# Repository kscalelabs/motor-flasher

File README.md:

# can-daddy-atopile

Wooohooo a new package!

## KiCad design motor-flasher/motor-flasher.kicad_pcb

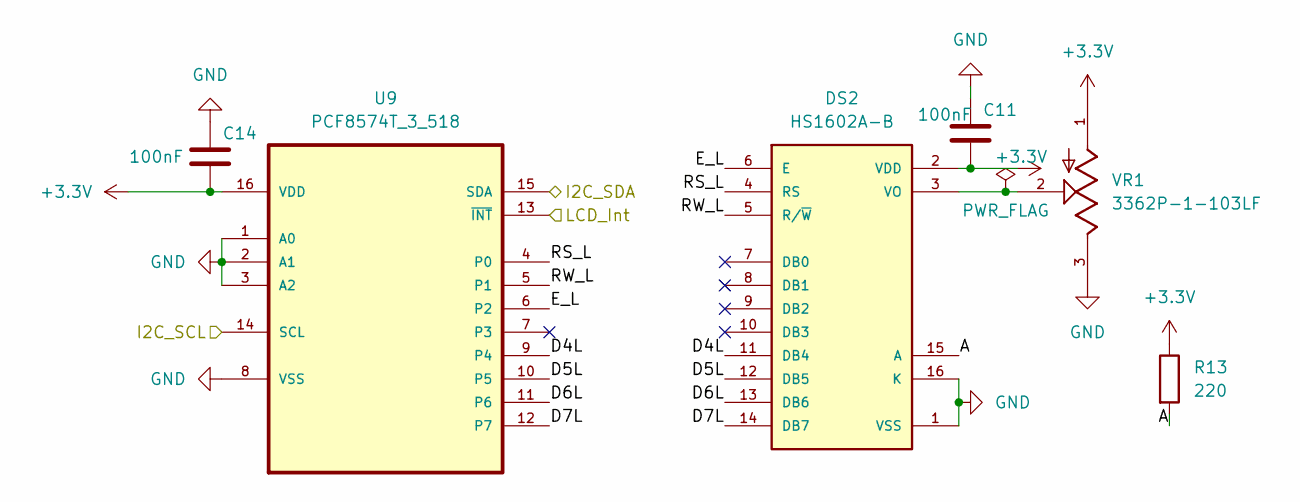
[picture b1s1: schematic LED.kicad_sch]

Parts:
C11, C14: 100nF; C_0402_1005Metric
DS2: HS1602A-B; LCD_LCM-S01602DTR_A
R13: 220; R_0402_1005Metric
U9: PCF8574T_3_518; SOIC127P1032X265-16N; MPN PCF8574T/3,518
VR1: 3362P-1-103LF; POT_3362P; PARTREV 08/26/10

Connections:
+3.3V: C11.2, C14.2, DS2.2 (VDD), R13.1, U9.16 (VDD), VR1.1; also elsewhere on the board
/LCD/A: DS2.15 (A), R13.2
/LCD/D4L: DS2.11 (DB4), U9.9 (P4)
/LCD/D5L: DS2.12 (DB5), U9.10 (P5)
/LCD/D6L: DS2.13 (DB6), U9.11 (P6)
/LCD/D7L: DS2.14 (DB7), U9.12 (P7)
/LCD/E_L: DS2.6 (E), U9.6 (P2)
/LCD/RS_L: DS2.4 (RS), U9.4 (P0)
/LCD/RW_L: DS2.5 (R/~W), U9.5 (P1)
/LCD_Int: U9.13 (~INT); also elsewhere on the board
/SCL: U9.14 (SCL); also elsewhere on the board
/SDA: U9.15 (SDA); also elsewhere on the board
GND: C11.1, C14.1, DS2.1 (VSS), DS2.16 (K), U9.1 (A0), U9.2 (A1), U9.3 (A2), U9.8 (VSS), VR1.3; also elsewhere on the board
unnamed: DS2.3 (VO), VR1.2

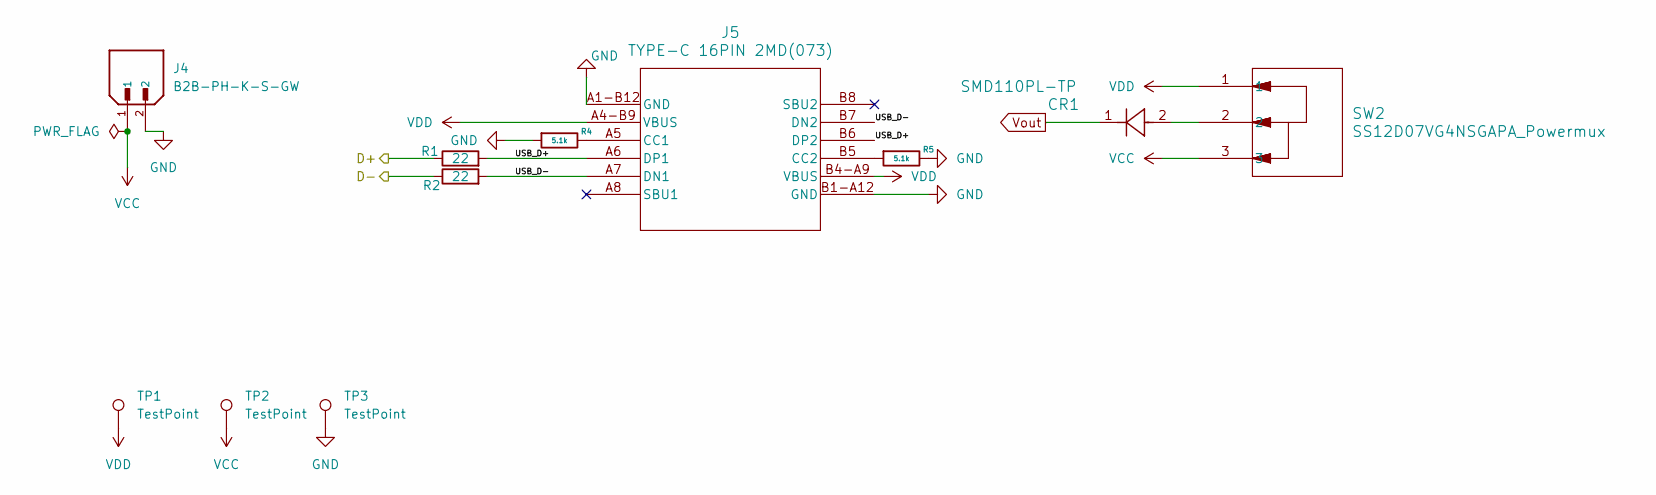
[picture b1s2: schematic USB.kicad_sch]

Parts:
CR1: SMD110PL-TP; SOD-123FL_MCC
J4: B2B-PH-K-S-GW; JST_B2B-XH-A; PARTREV N/A
J5: TYPE-C 16PIN 2MD(073); GCT_USB4105-GF-A
R1, R2: 22; R_0402_1005Metric
R4, R5: 5.1k; R_0603_1608Metric
SW2: SS12D07VG4NSGAPA_Powermux; SS12D07_CNK
TP1, TP2, TP3: TestPoint

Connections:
/D+: R1.1; also elsewhere on the board
/D-: R2.1; also elsewhere on the board
/USB + Power Source/USB_D+: J5.A6 (DP1), J5.B6 (DP2), R1.2
/USB + Power Source/USB_D-: J5.A7 (DN1), J5.B7 (DN2), R2.2
GND: J4.2, J5.A1-B12 (GND), J5.B1-A12 (GND), R4.2, R5.1, TP3.1; also elsewhere on the board
unnamed: CR1.2, SW2.2
unnamed: J5.A5 (CC1), R4.1
unnamed: J5.B5 (CC2), R5.2
VCC: J4.1, SW2.3, TP2.1
VDD: J5.A4-B9 (VBUS), J5.B4-A9 (VBUS), SW2.1, TP1.1
Vout: CR1.1; also elsewhere on the board

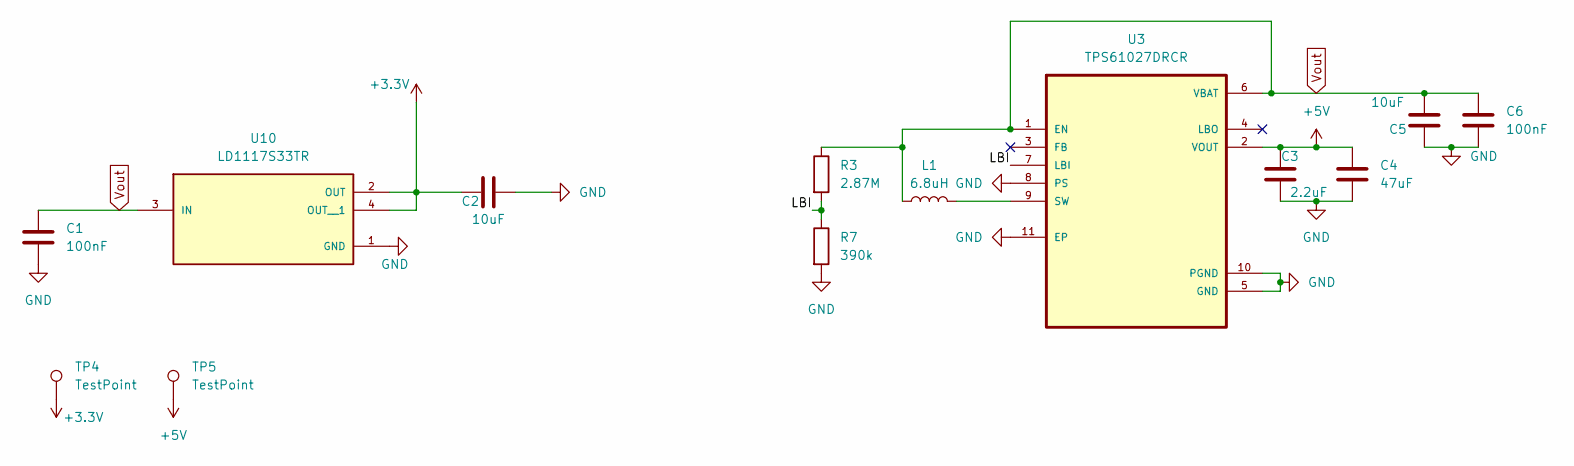
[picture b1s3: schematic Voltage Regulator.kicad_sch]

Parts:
C1, C6: 100nF; C_0402_1005Metric
C2, C5: 10uF; C_0805_2012Metric
C3: 2.2uF; C_0402_1005Metric
C4: 47uF; C_0805_2012Metric
L1: 6.8uH; CDRH5D28RHP
R3: 2.87M; R_0805_2012Metric
R7: 390k; R_0805_2012Metric
TP4, TP5: TestPoint
U3: TPS61027DRCR; VREG_V62_16624-01YE
U10: LD1117S33TR; SOT230P700X180-4N

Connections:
+3.3V: C2.2, TP4.1, U10.2 (OUT), U10.4 (OUT__1); also elsewhere on the board
+5V: C3.1, C4.1, TP5.1, U3.2 (VOUT); also elsewhere on the board
/Voltage Regulator/LBI: R3.2, R7.1, U3.7 (LBI)
GND: C1.2, C2.1, C3.2, C4.2, C5.1, C6.1, R7.2, U3.5 (GND), U3.8 (PS), U3.10 (PGND), U3.11 (EP), U10.1 (GND); also elsewhere on the board
unnamed: L1.2, U3.9 (SW)
Vout: C1.1, C5.2, C6.2, L1.1, R3.1, U3.1 (EN), U3.6 (VBAT), U10.3 (IN); also elsewhere on the board

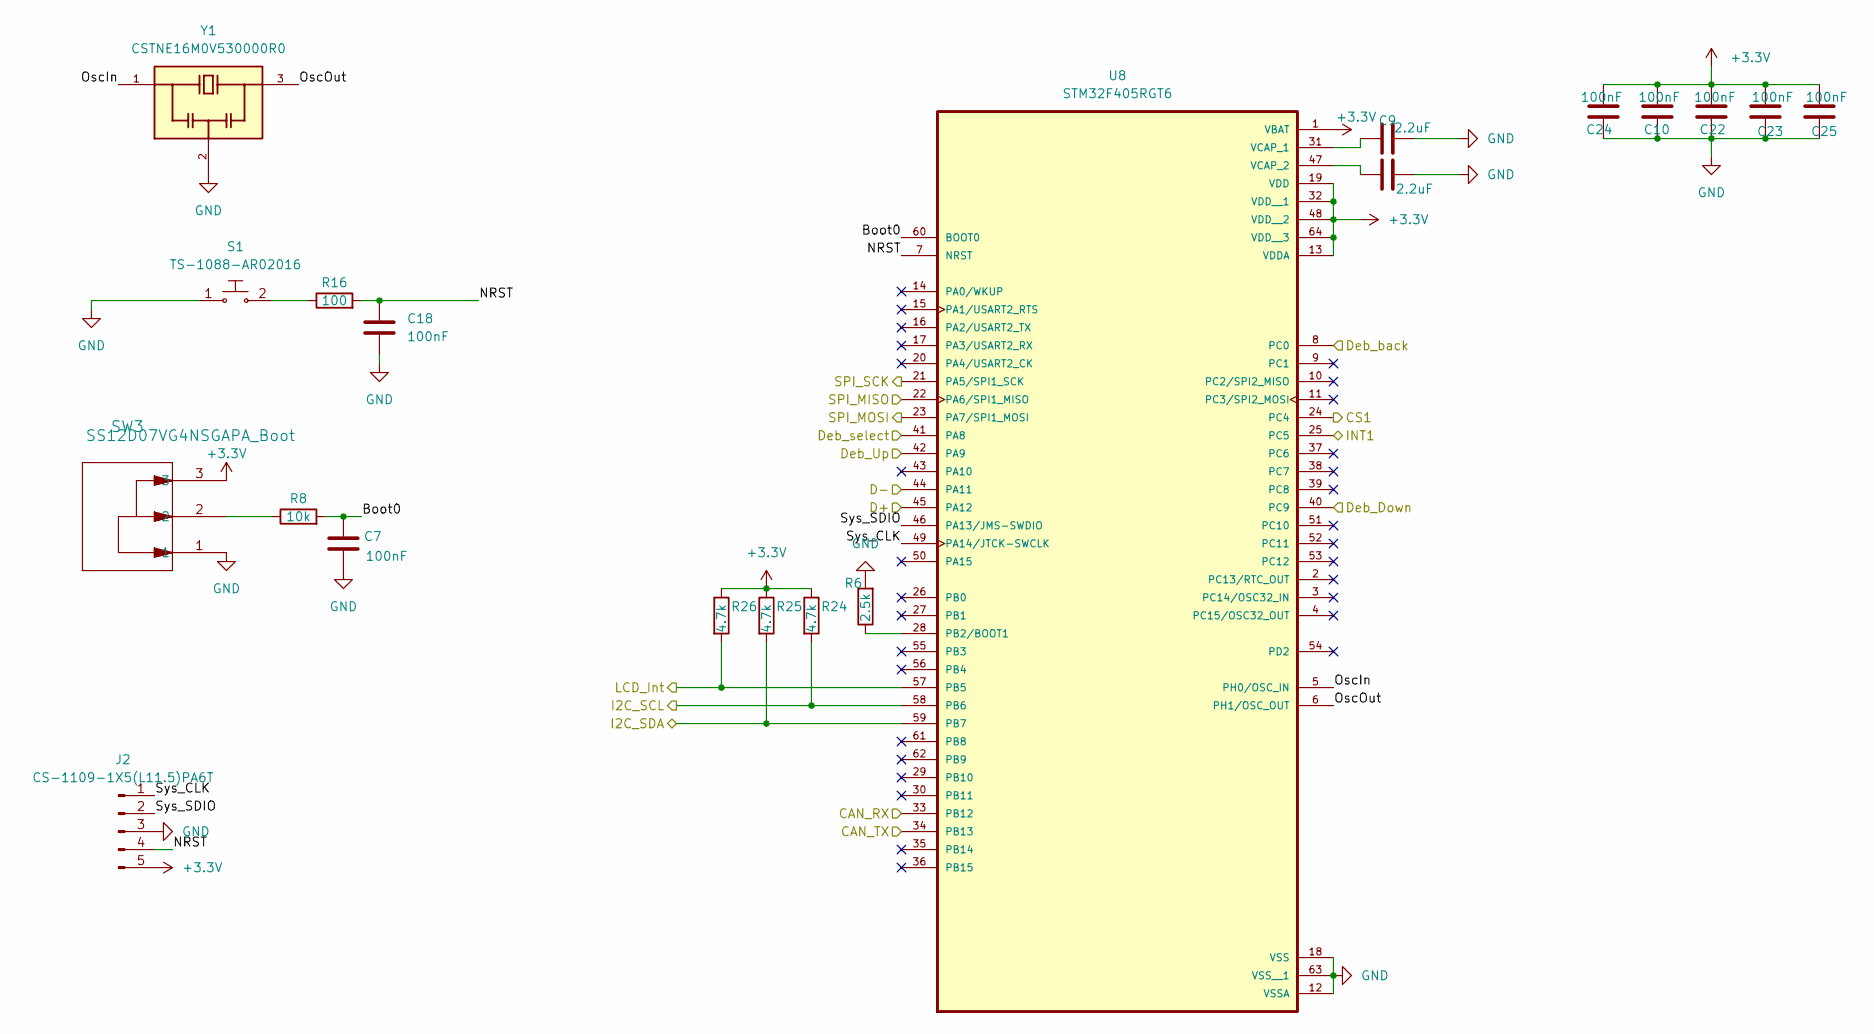
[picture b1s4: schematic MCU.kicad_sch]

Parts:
C7, C10, C18, C22, C23, C24, C25: 100nF; C_0402_1005Metric
C8, C9: 2.2uF; C_0402_1005Metric
J2: CS-1109-1X5(L11.5)PA6T; PinHeader_1x05_P2.54mm_Horizontal
R6: 2.5k; R_0603_1608Metric
R8: 10k; R_0402_1005Metric
R16: 100; R_0402_1005Metric
R24, R25, R26: 4.7k; R_0402_1005Metric
S1: TS-1088-AR02016; MPN GPTS203211B; Digi-Key_PN CW181-ND
SW3: SS12D07VG4NSGAPA_Boot; SS12D07_CNK
U8: STM32F405RGT6; QFP50P1200X1200X160-64N; PARTREV LTR
Y1: CSTNE16M0V530000R0; OSC_CSTNE16M0V530000R0; PARTREV JGC42-8853B

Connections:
+3.3V: C10.1, C22.1, C23.1, C24.1, C25.1, J2.5, R24.1, R25.1, R26.1, SW3.3, U8.1 (VBAT), U8.13 (VDDA), U8.19 (VDD), U8.32 (VDD__1), U8.48 (VDD__2), U8.64 (VDD__3); also elsewhere on the board
/CANRX: U8.33 (PB12); also elsewhere on the board
/CANTX: U8.34 (PB13); also elsewhere on the board
/CS: U8.24 (PC4); also elsewhere on the board
/D+: U8.45 (PA12); also elsewhere on the board
/D-: U8.44 (PA11); also elsewhere on the board
/Deb_Down: U8.40 (PC9); also elsewhere on the board
/Deb_Up: U8.42 (PA9); also elsewhere on the board
/Deb_back: U8.8 (PC0); also elsewhere on the board
/Deb_select: U8.41 (PA8); also elsewhere on the board
/INT: U8.25 (PC5); also elsewhere on the board
/LCD_Int: R26.2, U8.57 (PB5); also elsewhere on the board
/MCU/Boot0: C7.1, R8.2, U8.60 (BOOT0)
/MCU/NRST: C18.1, J2.4, R16.2, U8.7 (NRST)
/MCU/OscIn: U8.5 (PH0/OSC_IN), Y1.1
/MCU/OscOut: U8.6 (PH1/OSC_OUT), Y1.3
/MCU/Sys_CLK: J2.1, U8.49 (PA14/JTCK-SWCLK)
/MCU/Sys_SDIO: J2.2, U8.46 (PA13/JMS-SWDIO)
/MISO: U8.22 (PA6/SPI1_MISO); also elsewhere on the board
/MOSI: U8.23 (PA7/SPI1_MOSI); also elsewhere on the board
/SCK: U8.21 (PA5/SPI1_SCK); also elsewhere on the board
/SCL: R24.2, U8.58 (PB6); also elsewhere on the board
/SDA: R25.2, U8.59 (PB7); also elsewhere on the board
GND: C7.2, C8.2, C9.2, C10.2, C18.2, C22.2, C23.2, C24.2, C25.2, J2.3, R6.2, S1.1, SW3.1, U8.12 (VSSA), U8.18 (VSS), U8.63 (VSS__1), Y1.2; also elsewhere on the board
unnamed: R8.1, SW3.2
unnamed: R16.1, S1.2
unnamed: R6.1, U8.28 (PB2/BOOT1)
unnamed: C8.1, U8.31 (VCAP_1)
unnamed: C9.1, U8.47 (VCAP_2)

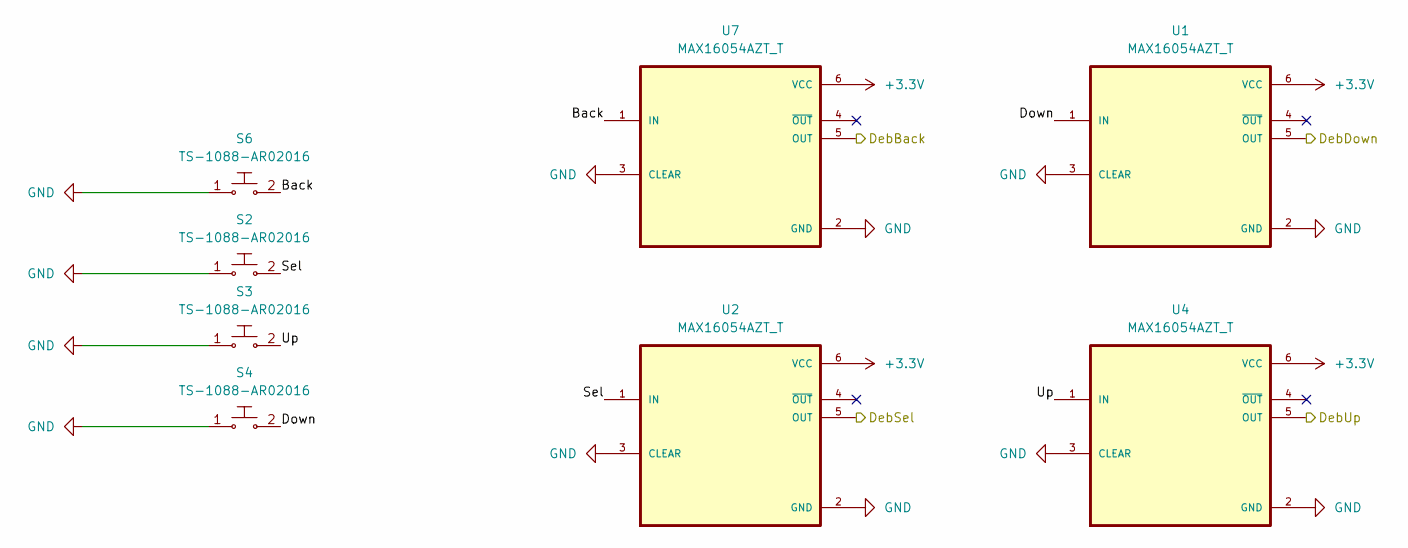
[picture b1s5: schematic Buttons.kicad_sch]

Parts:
S2, S3, S4, S6: TS-1088-AR02016; MPN GPTS203211B; Digi-Key_PN CW181-ND
U1, U2, U4, U7: MAX16054AZT_T; SOT95P275X110-6N

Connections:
+3.3V: U1.6 (VCC), U2.6 (VCC), U4.6 (VCC), U7.6 (VCC); also elsewhere on the board
/Buttons/Back: S6.2, U7.1 (IN)
/Buttons/Down: S4.2, U1.1 (IN)
/Buttons/Sel: S2.2, U2.1 (IN)
/Buttons/Up: S3.2, U4.1 (IN)
/Deb_Down: U1.5 (OUT); also elsewhere on the board
/Deb_Up: U4.5 (OUT); also elsewhere on the board
/Deb_back: U7.5 (OUT); also elsewhere on the board
/Deb_select: U2.5 (OUT); also elsewhere on the board
GND: S2.1, S3.1, S4.1, S6.1, U1.2 (GND), U1.3 (CLEAR), U2.2 (GND), U2.3 (CLEAR), U4.2 (GND), U4.3 (CLEAR), U7.2 (GND), U7.3 (CLEAR); also elsewhere on the board

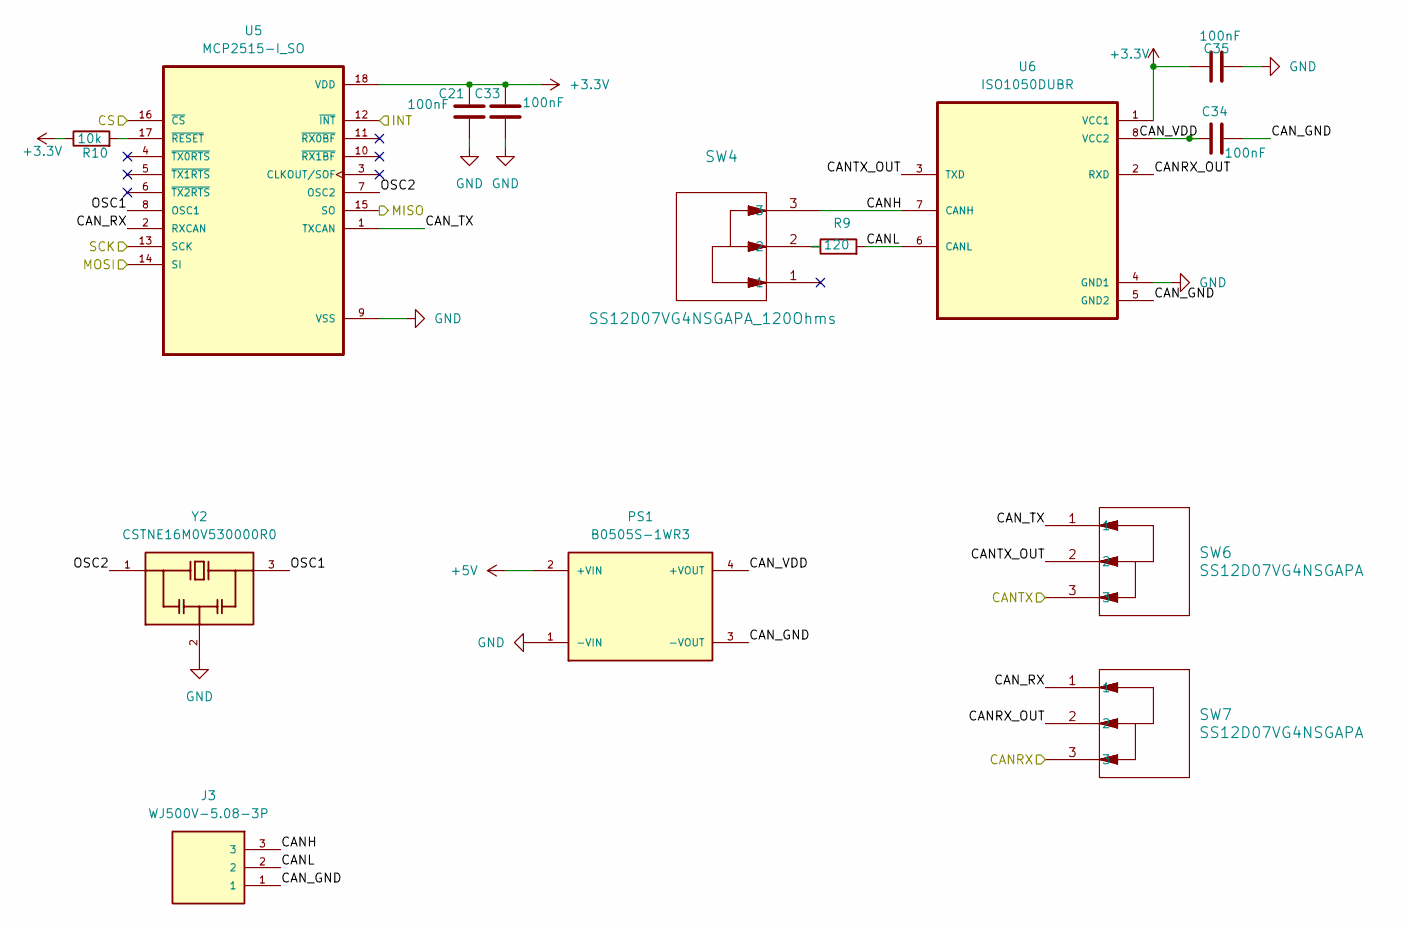
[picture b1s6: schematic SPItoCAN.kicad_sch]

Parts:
C21, C33, C34, C35: 100nF; C_0402_1005Metric
J3: WJ500V-5.08-3P; CUI_TB006-508-03BE
PS1: B0505S-1WR3; CONV_RFM-0505S; PARTREV 0
R9: 120; R_0402_1005Metric
R10: 10k; R_0402_1005Metric
SW4: SS12D07VG4NSGAPA_120Ohms; SS12D07_CNK
SW6, SW7: SS12D07VG4NSGAPA; SS12D07_CNK
U5: MCP2515-I_SO; SOIC127P1030X265-18N
U6: ISO1050DUBR; SOP254P1040X485-8N
Y2: CSTNE16M0V530000R0; OSC_CSTNE16M0V530000R0; PARTREV JGC42-8853B

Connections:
+3.3V: C21.2, C33.2, C35.1, R10.1, U5.18 (VDD), U6.1 (VCC1); also elsewhere on the board
+5V: PS1.2 (+VIN); also elsewhere on the board
/CAN1/CANH: J3.3, SW4.3, U6.7 (CANH)
/CAN1/CANL: J3.2, R9.2, U6.6 (CANL)
/CAN1/CANRX_OUT: SW7.2, U6.2 (RXD)
/CAN1/CANTX_OUT: SW6.2, U6.3 (TXD)
/CAN1/CAN_GND: C34.2, J3.1, PS1.3 (-VOUT), U6.5 (GND2)
/CAN1/CAN_RX: SW7.1, U5.2 (RXCAN)
/CAN1/CAN_TX: SW6.1, U5.1 (TXCAN)
/CAN1/CAN_VDD: C34.1, PS1.4 (+VOUT), U6.8 (VCC2)
/CAN1/OSC1: U5.8 (OSC1), Y2.3
/CAN1/OSC2: U5.7 (OSC2), Y2.1
/CANRX: SW7.3; also elsewhere on the board
/CANTX: SW6.3; also elsewhere on the board
/CS: U5.16 (~CS); also elsewhere on the board
/INT: U5.12 (~INT); also elsewhere on the board
/MISO: U5.15 (SO); also elsewhere on the board
/MOSI: U5.14 (SI); also elsewhere on the board
/SCK: U5.13 (SCK); also elsewhere on the board
GND: C21.1, C33.1, C35.2, PS1.1 (-VIN), U5.9 (VSS), U6.4 (GND1), Y2.2; also elsewhere on the board
unnamed: R9.1, SW4.2
unnamed: R10.2, U5.17 (~RESET)

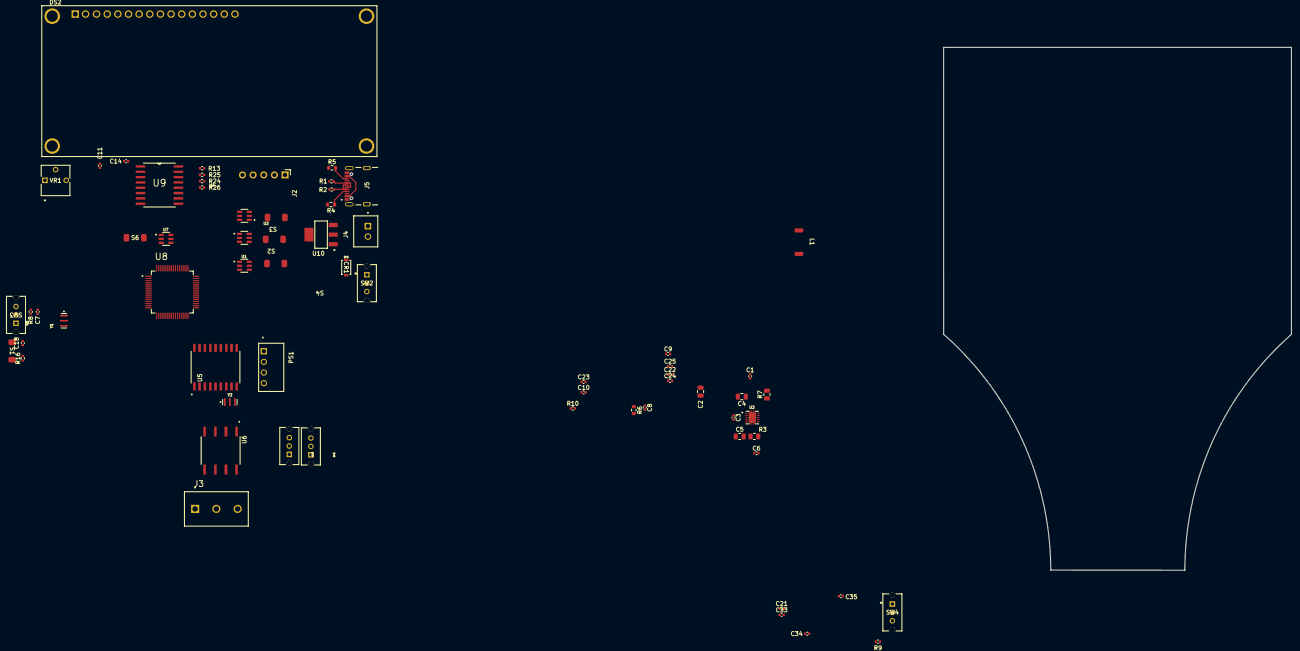
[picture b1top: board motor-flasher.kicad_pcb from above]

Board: 4 copper layers, 83.0 x 124.8 mm, 67 parts (0 on the bottom side), 65 nets.

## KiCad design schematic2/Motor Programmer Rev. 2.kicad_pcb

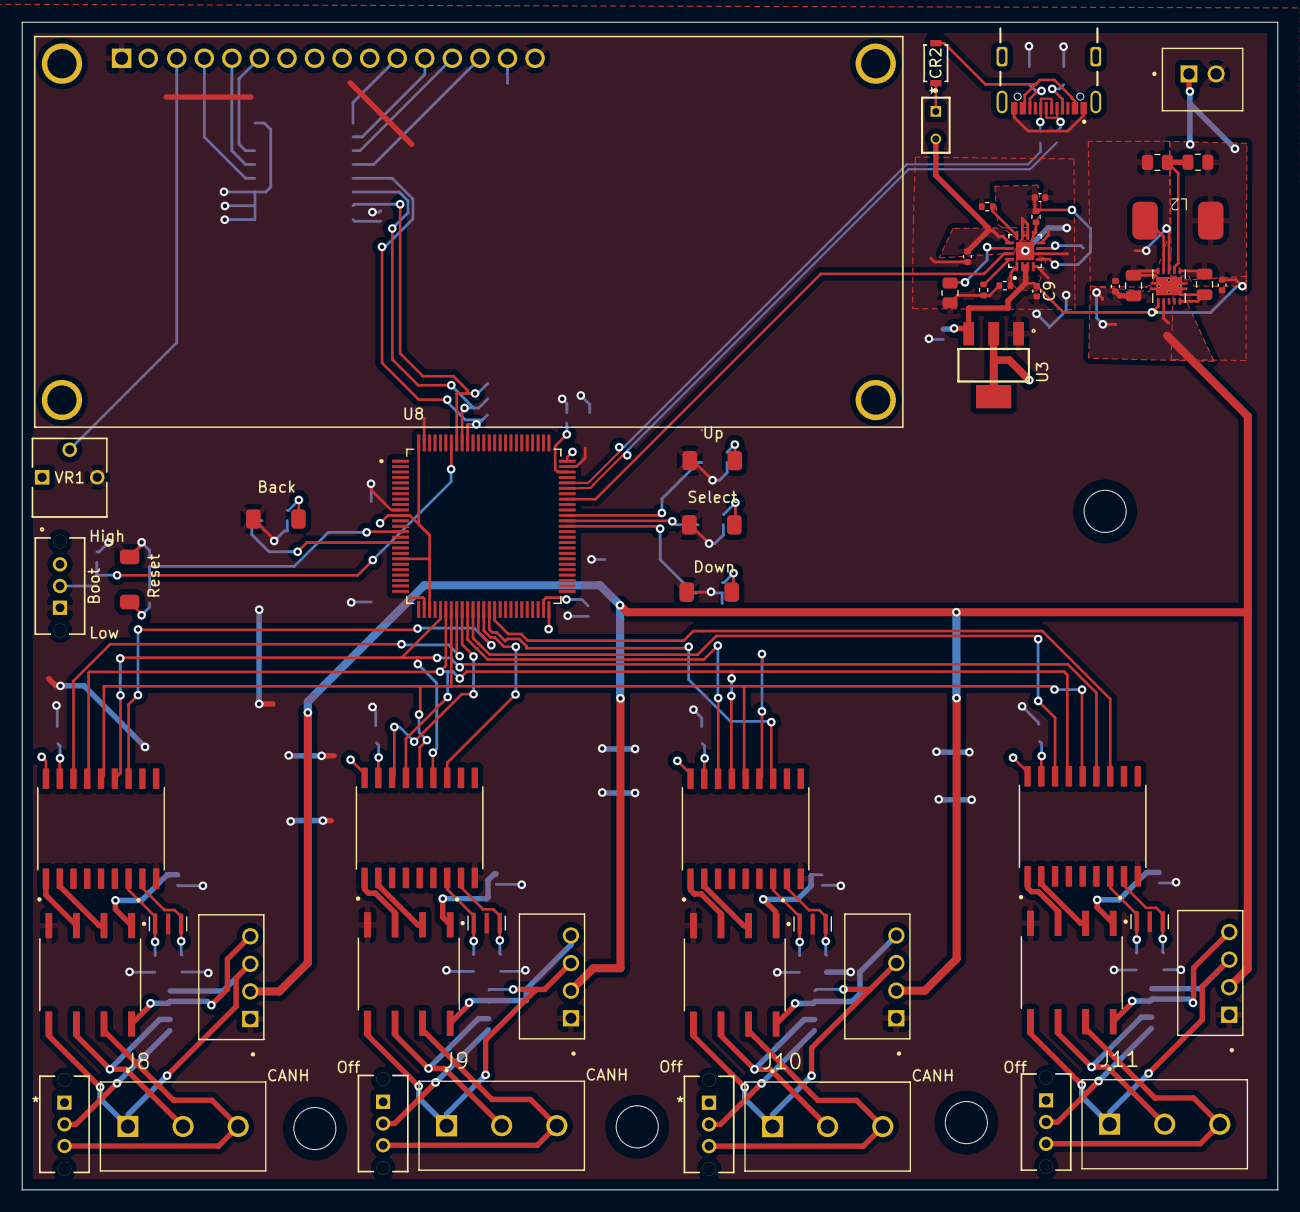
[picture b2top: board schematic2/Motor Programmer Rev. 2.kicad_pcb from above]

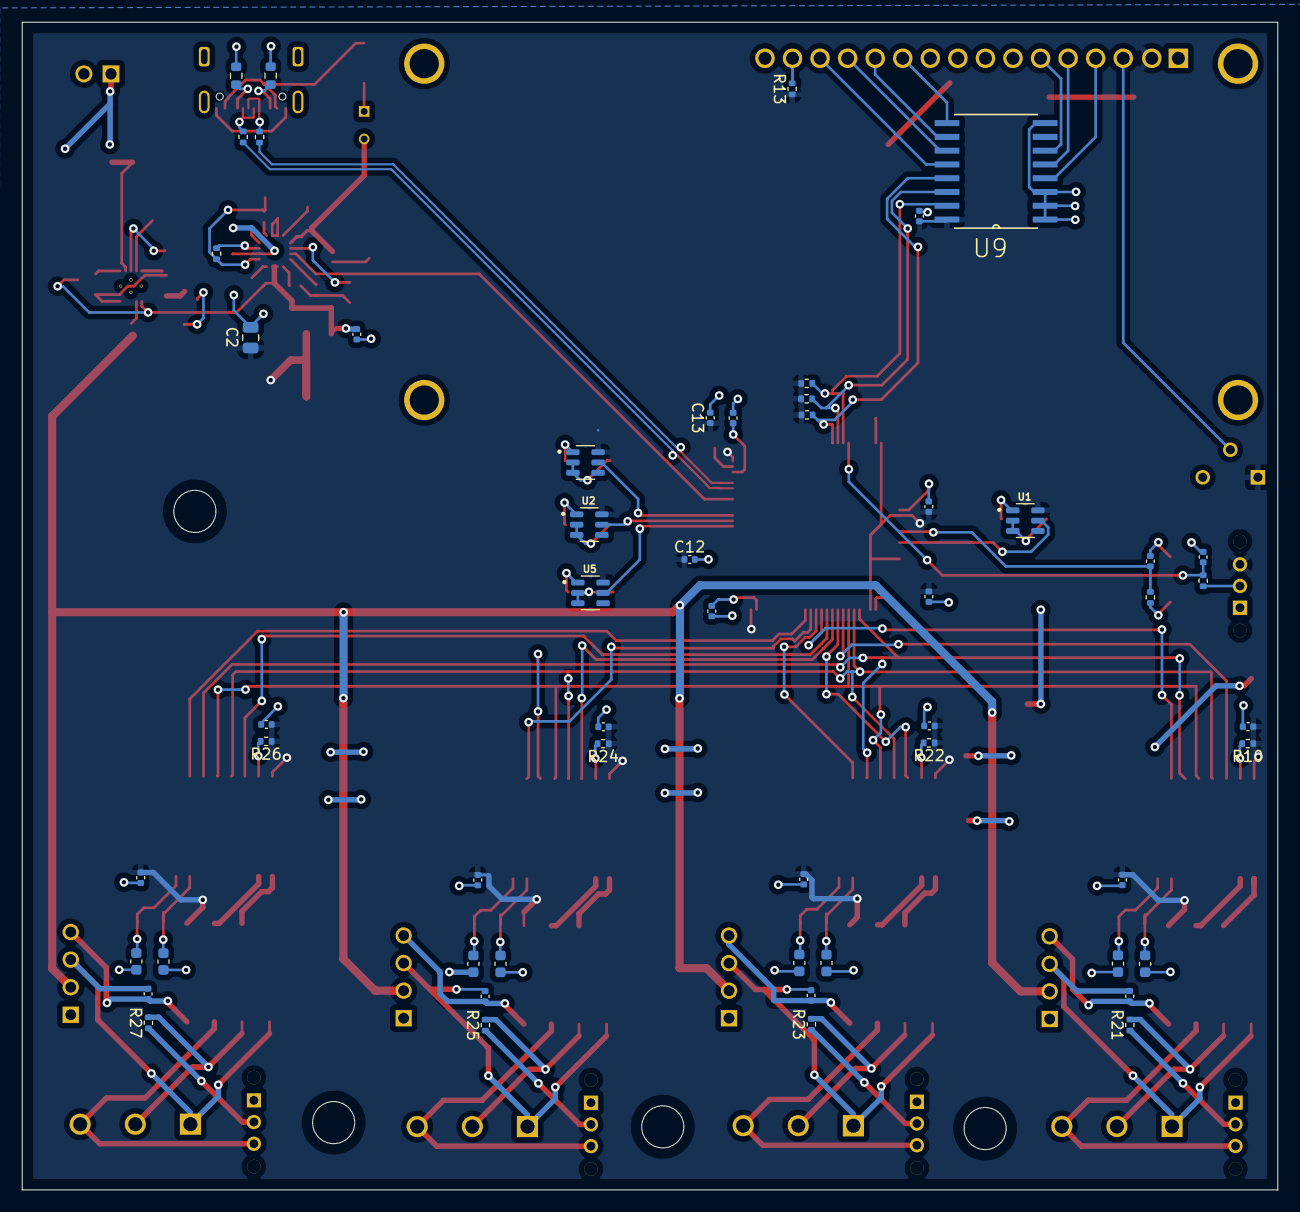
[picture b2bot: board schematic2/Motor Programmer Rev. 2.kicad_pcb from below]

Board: 2 copper layers, 115.7 x 107.6 mm, 110 parts (55 on the bottom side), 100 nets.

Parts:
C1, C4, C7, C11, C12, C13, C14, C15, C18, C33, C34, C35, C38, C39, C40, C43, C44, C45, C48, C49, C50: 100nF; C_0402_1005Metric
C2, C3: 10uF; C_0805_2012Metric
C5, C16, C17: 2.2uF; C_0402_1005Metric
C6: 47uF; C_0805_2012Metric
C8: 1uF; C_0402_1005Metric
C9, C10: 4.7uF; C_0402_1005Metric
C31, C32, C36, C37, C41, C42, C46, C47: 7pF; C_0603_1608Metric
CR2: SMD110PL-TP; SOD-123FL_MCC
DS1: HS1602A-B; LCD_LCM-S01602DTR_A
J1: USB4105-GF-A; GCT_USB4105-GF-A
J4: B2B-PH-K-S-GW; JST_B2B-XH-A
J8, J9, J10, J11: WJ500V-5.08-3P; CUI_TB006-508-03BE
J12: TS-102-G-A; SAMTEC_TS-102-G-A
L2: 6.8uH; CDRH5D28RHP
PS5, PS6, PS7, PS8: B0505S-1WR3; CONV_RFM-0505S
R1, R2: 22; R_0402_1005Metric
R3: 2.87M; R_0805_2012Metric
R4, R5: 5.1k; R_0603_1608Metric
R7: 390k; R_0805_2012Metric
R8, R9, R10, R11, R12, R13, R22, R24, R26: 10k; R_0402_1005Metric
R14: 1.18K; R_0402_1005Metric
R15: 25k; R_0805_2012Metric
R16: 100; R_0402_1005Metric
R17: 1.5k; R_0402_1005Metric
R18, R19, R20: 4.7k; R_0402_1005Metric
R21, R23, R25, R27: 120; R_0402_1005Metric
S5, S10, S11, S12, S13: TS-1088-AR02016
SW1, SW2, SW3, SW4, SW5: SS12D07VG4NSGAPA; SS12D07_CNK
U1, U2, U4, U5: MAX16054AZT_T; SOT95P275X110-6N
U3: LD1117S33TR; SOT230P700X180-4N
U6: TPS61027DRCR; VREG_V62_16624-01YE
U7: BQ24075RGTT; QFN50P300X300X100-17N
U8: STM32F407VGT6; QFP50P1600X1600X160-100N
U9: PCF8574T_3_518; SOIC127P1032X265-16N
U19, U21, U23, U25: MCP2515-I_SO; SOIC127P1030X265-18N
U20, U22, U24, U26: ISO1050DUBR; SOP254P1040X485-8N
VR1: 3362P-1-103LF; POT_3362P
Y2, Y3, Y4, Y5: CSTNE16M0V530000R0; OSC_CSTNE16M0V530000R0

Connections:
+3.3V: C2.2, C11.1, C12.1, C13.1, C14.2, C15.1, C33.2, C35.1, C38.2, C40.1, C43.2, C45.1, C48.2, C50.1, DS1.2 (VDD), R10.1, R13.1, R18.1, R19.1, R20.1, R22.1, R24.1, R26.1, SW5.3, U1.6 (VCC), U2.6 (VCC), U3.2 (OUT), U3.4 (OUT__1), U4.6 (VCC), U5.6 (VCC), U8.11 (VDD), U8.19 (VDD__1), U8.28 (VDD__2), U8.50 (VDD__3), U8.75 (VDD__4), U8.100 (VDD__5), U9.16 (VDD), U19.18 (VDD), U20.1 (VCC1), U21.18 (VDD), U22.1 (VCC1), U23.18 (VDD), U24.1 (VCC1), U25.18 (VDD), U26.1 (VCC1), VR1.1
+5V: C5.1, C6.1, PS5.2 (+VIN), PS6.2 (+VIN), PS7.2 (+VIN), PS8.2 (+VIN), U6.2 (VOUT)
/Buttons/Back: S5.2, U1.1 (IN)
/Buttons/Down: S13.2, U5.1 (IN)
/Buttons/Sel: S11.2, U2.1 (IN)
/Buttons/Up: S12.2, U4.1 (IN)
/CAN1/CANH: J8.3, SW1.3, U20.7 (CANH)
/CAN1/CANL: J8.2, R21.2, U20.6 (CANL)
/CAN1/CAN_GND: C34.2, J8.1, PS5.3 (-VOUT), U20.5 (GND2)
/CAN1/CAN_RX: U19.2 (RXCAN), U20.2 (RXD)
/CAN1/CAN_TX: U19.1 (TXCAN), U20.3 (TXD)
/CAN1/CAN_VDD: C34.1, PS5.4 (+VOUT), U20.8 (VCC2)
/CAN1/OSC1: C32.1, U19.8 (OSC1), Y2.3
/CAN1/OSC2: C31.1, U19.7 (OSC2), Y2.1
/CAN2/CANH: J9.3, SW2.3, U22.7 (CANH)
/CAN2/CANL: J9.2, R23.2, U22.6 (CANL)
/CAN2/CAN_GND: C39.2, J9.1, PS6.3 (-VOUT), U22.5 (GND2)
/CAN2/CAN_RX: U21.2 (RXCAN), U22.2 (RXD)
/CAN2/CAN_TX: U21.1 (TXCAN), U22.3 (TXD)
/CAN2/CAN_VDD: C39.1, PS6.4 (+VOUT), U22.8 (VCC2)
/CAN2/OSC1: C37.1, U21.8 (OSC1), Y3.3
/CAN2/OSC2: C36.1, U21.7 (OSC2), Y3.1
/CAN3/CANH: J10.3, SW3.3, U24.7 (CANH)
/CAN3/CANL: J10.2, R25.2, U24.6 (CANL)
/CAN3/CAN_GND: C44.2, J10.1, PS7.3 (-VOUT), U24.5 (GND2)
/CAN3/CAN_RX: U23.2 (RXCAN), U24.2 (RXD)
/CAN3/CAN_TX: U23.1 (TXCAN), U24.3 (TXD)
/CAN3/CAN_VDD: C44.1, PS7.4 (+VOUT), U24.8 (VCC2)
/CAN3/OSC1: C42.1, U23.8 (OSC1), Y4.3
/CAN3/OSC2: C41.1, U23.7 (OSC2), Y4.1
/CAN4/CANH: J11.3, SW4.3, U26.7 (CANH)
/CAN4/CANL: J11.2, R27.2, U26.6 (CANL)
/CAN4/CAN_GND: C49.2, J11.1, PS8.3 (-VOUT), U26.5 (GND2)
/CAN4/CAN_RX: U25.2 (RXCAN), U26.2 (RXD)
/CAN4/CAN_TX: U25.1 (TXCAN), U26.3 (TXD)
/CAN4/CAN_VDD: C49.1, PS8.4 (+VOUT), U26.8 (VCC2)
/CAN4/OSC1: C47.1, U25.8 (OSC1), Y5.3
/CAN4/OSC2: C46.1, U25.7 (OSC2), Y5.1
/CS1: U8.33 (PC4), U19.16 (~CS)
/CS2: U8.34 (PC5), U21.16 (~CS)
/CS3: U8.35 (PB0), U23.16 (~CS)
/CS4: U8.36 (PB1), U25.16 (~CS)
/D+: R1.1, U8.71 (PA12)
/D-: R2.1, U8.70 (PA11)
/Deb_Down: U5.5 (OUT), U8.63 (PC6)
/Deb_Up: U4.5 (OUT), U8.65 (PC8)
/Deb_back: U1.5 (OUT), U8.16 (PC1)
/Deb_select: U2.5 (OUT), U8.64 (PC7)
/INT1: U8.37 (PB2), U19.12 (~INT)
/INT2: U8.38 (PE7), U21.12 (~INT)
/INT3: U8.39 (PE8), U23.12 (~INT)
/INT4: U8.40 (PE9), U25.12 (~INT)
/LCD_Int: R20.2, U8.91 (PB5), U9.13 (~INT)
/LED/A: DS1.15 (A), R13.2
/LED/D4L: DS1.11 (DB4), U9.9 (P4)
/LED/D5L: DS1.12 (DB5), U9.10 (P5)
/LED/D6L: DS1.13 (DB6), U9.11 (P6)
/LED/D7L: DS1.14 (DB7), U9.12 (P7)
/LED/E_L: DS1.6 (E), U9.6 (P2)
/LED/RS_L: DS1.4 (RS), U9.4 (P0)
/LED/RW_L: DS1.5 (R/~W), U9.5 (P1)
/MCU/Boot0: C7.2, R8.2, U8.94 (BOOT0)
/MCU/NRST: C18.1, R16.2, U8.14 (NRST)
/MISO: U8.31 (PA6), U19.15 (SO), U21.15 (SO), U23.15 (SO), U25.15 (SO)
/MOSI: U8.32 (PA7), U19.14 (SI), U21.14 (SI), U23.14 (SI), U25.14 (SI)
/SCK: U8.30 (PA5), U19.13 (SCK), U21.13 (SCK), U23.13 (SCK), U25.13 (SCK)
/SCL: R19.2, U8.92 (PB6), U9.14 (SCL)
/SDA: R18.2, U8.93 (PB7), U9.15 (SDA)
/SysOff: U7.15 (SYSOFF), U8.68 (PA9)
/USB + Power Source/ILIM: R14.1, U7.12 (ILIM)
/USB + Power Source/Iset: R17.1, U7.16 (ISET)
/USB + Power Source/LBI: R3.2, R7.1, U6.7 (LBI)
/USB + Power Source/TMR: R15.1, U7.14 (TMR)
/USB + Power Source/USB_D+: J1.A6 (DP1), J1.B6 (DP2), R1.2
/USB + Power Source/USB_D-: J1.A7 (DN1), J1.B7 (DN2), R2.2
/USB + Power Source/USB_VBUS: CR2.2, J1.A4-B9 (VBUS), J1.B4-A9 (VBUS)
GND: C1.2, C2.1, C3.2, C4.2, C5.2, C6.2, C7.1, C8.2, C9.2, C10.2, C11.2, C12.2, C13.2, C14.1, C15.2, C16.2, C17.2, C18.2, C31.2, C32.2, C33.1, C35.2, C36.2, C37.2, C38.1, C40.2, C41.2, C42.2, C43.1, C45.2, C46.2, C47.2, C48.1, C50.2, DS1.1 (VSS), DS1.16 (K), J1.A1-B12 (GND), J1.B1-A12 (GND), J4.2, PS5.1 (-VIN), PS6.1 (-VIN), PS7.1 (-VIN), PS8.1 (-VIN), R4.2, R5.1, R7.2, R9.1, R14.2, R15.2, R17.2, S5.1, S10.2, S11.1, S12.1, S13.1, SW5.1, U1.2 (GND), U1.3 (CLEAR), U2.2 (GND), U2.3 (CLEAR), U3.1 (GND), U4.2 (GND), U4.3 (CLEAR), U5.2 (GND), U5.3 (CLEAR), U6.5 (GND), U6.8 (PS), U6.10 (PGND), U6.11 (EP), U7.4 (~CE), U7.6 (EN1), U7.8 (VSS), U7.17 (EP), U8.10 (VSS), U8.27 (VSS__1), U8.74 (VSS__2), U8.99 (VSS__3), U9.1 (A0), U9.2 (A1), U9.3 (A2), U9.8 (VSS), U19.9 (VSS), U20.4 (GND1), U21.9 (VSS), U22.4 (GND1), U23.9 (VSS), U24.4 (GND1), U25.9 (VSS), U26.4 (GND1), VR1.3, Y2.2, Y3.2, Y4.2, Y5.2
unnamed: CR2.1, J12.01
unnamed: DS1.3 (VO), VR1.2
unnamed: J1.A5 (CC1), R4.1
unnamed: J1.B5 (CC2), R5.2
unnamed: R8.1, SW5.2
unnamed: R16.1, S10.1
unnamed: R21.1, SW1.2
unnamed: R23.1, SW2.2
unnamed: R25.1, SW3.2
unnamed: R27.1, SW4.2
unnamed: L2.2, U6.9 (SW)
unnamed: C10.1, R11.2, R12.2, U7.5 (EN2), U7.10 (OUT), U7.11 (OUT__1)
unnamed: R9.2, U7.1 (TS)
unnamed: R12.1, U7.9 (~CHG)
unnamed: R11.1, U7.7 (~PGOOD)
unnamed: C16.1, U8.49 (VCAP_1)
unnamed: C17.1, U8.73 (VCAP_2)
unnamed: R10.2, U19.17 (~RESET)
unnamed: R22.2, U21.17 (~RESET)
unnamed: R24.2, U23.17 (~RESET)
unnamed: R26.2, U25.17 (~RESET)
VCC: C1.1, C3.1, C4.1, C9.1, J4.1, L2.1, R3.1, U3.3 (IN), U6.1 (EN), U6.6 (VBAT), U7.2 (BAT), U7.3 (BAT__1)
VDD: C8.1, J12.02, U7.13 (IN)

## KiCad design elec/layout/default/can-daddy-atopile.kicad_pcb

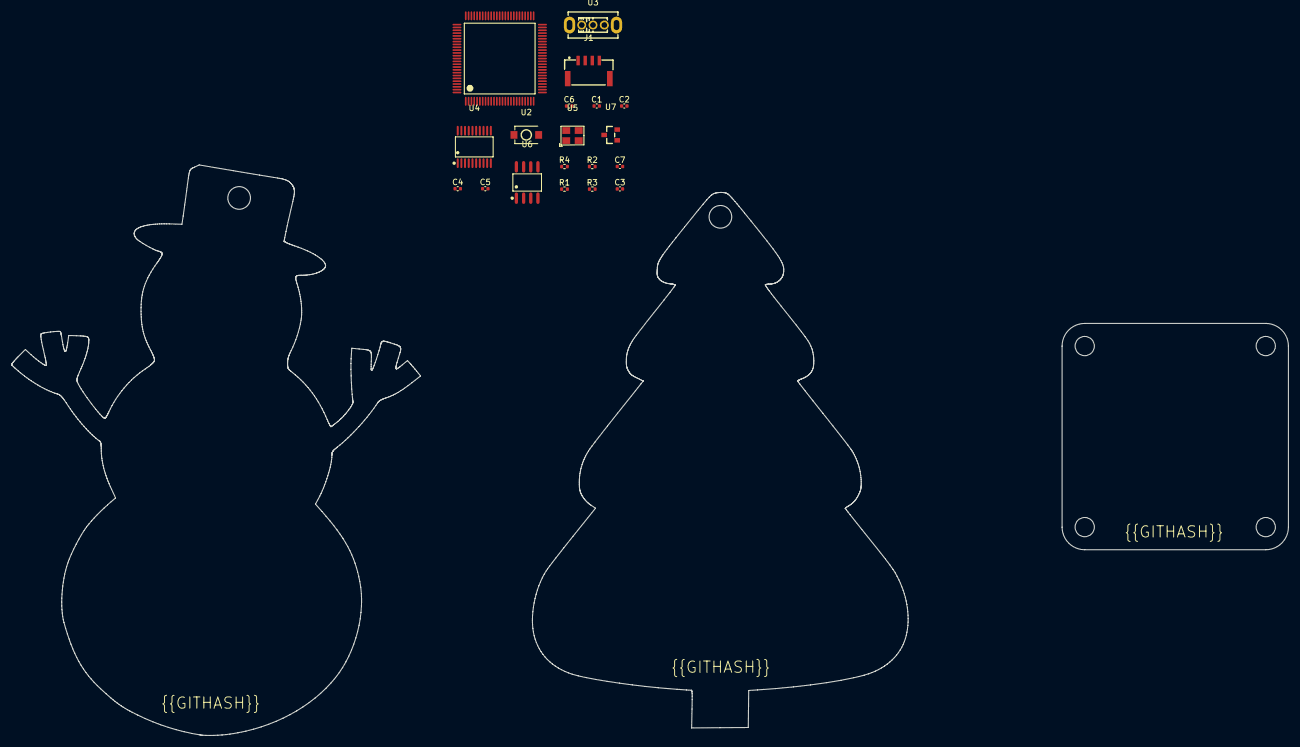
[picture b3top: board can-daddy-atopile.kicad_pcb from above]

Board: 2 copper layers, 19 parts (0 on the bottom side), 17 nets, no tracks yet.

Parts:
C1, C4, C5: 16V 100nF X7R ±10% 0402 Multilayer Ceramic Capaci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; C0402
C2, C3: 50V 9pF C0G 0402 Multilayer Ceramic Capacitors ML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; C0402
C6, C7: 25V 47nF X7R ±10% 0402 Multilayer Ceramic Capacit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; C0402
J1: CONN-SMD_4P-P1.25_SM04B-GHS-TB-LF-SN
R1, R2: 62.5mW Thick Film Resistors 50V ±100ppm/℃ ±1% 4.7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; R0402
R3: 62.5mW Thick Film Resistors 50V ±100ppm/℃ ±1% 10k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; R0402
R4: 62.5mW Thick Film Resistors 50V ±100ppm/℃ ±1% 120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; R0402
U1: LQFP-100_L14.0-W14.0-P0.50-LS16.0-BL
U2: SW-SMD_L3.9-W3.0-P4.45
U3: SW-TH_SS12D07VG4
U4: TSSOP-20_L6.5-W4.4-P0.65-LS6.4-BL
U5: OSC-SMD_4P-L3.2-W2.5-BL
U6: SOIC-8_L4.9-W3.9-P1.27-LS6.0-BL
U7: SOT-23_L2.9-W1.3-P1.90-LS2.4-BR

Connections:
can-gnd: C1.2, C2.2, C3.2, C4.2, C5.2, C6.2, C7.2, J1.4, R3.2, U4.10, U5.2, U5.4, U6.2, U7.3
can-vcc: C1.1, C4.1, U4.20, U6.5
can-vcc-1: C5.1, J1.1, U6.3
can.controller-vcc: C2.1, U4.8, U5.1
can.controller-vcc-1: C3.1, U4.9, U5.3
can.transceiver-vcc: R3.1, U6.8
canh: C7.1, J1.2, R4.2, U6.7, U7.2
canl: C6.1, J1.3, R4.1, U6.6, U7.1
micro.micro-gnd: U1.10, U1.27, U1.74, U1.99
micro.micro-vcc: R1.2, R2.2, U1.11, U1.19, U1.28, U1.50, U1.75, U1.100
miso: U1.31, U4.16
mosi: U1.32, U4.17
rx: U4.2, U6.4
sck: U1.30, U4.14
scl: R2.1, U1.92
sda: R1.1, U1.93
tx: U4.1, U6.1

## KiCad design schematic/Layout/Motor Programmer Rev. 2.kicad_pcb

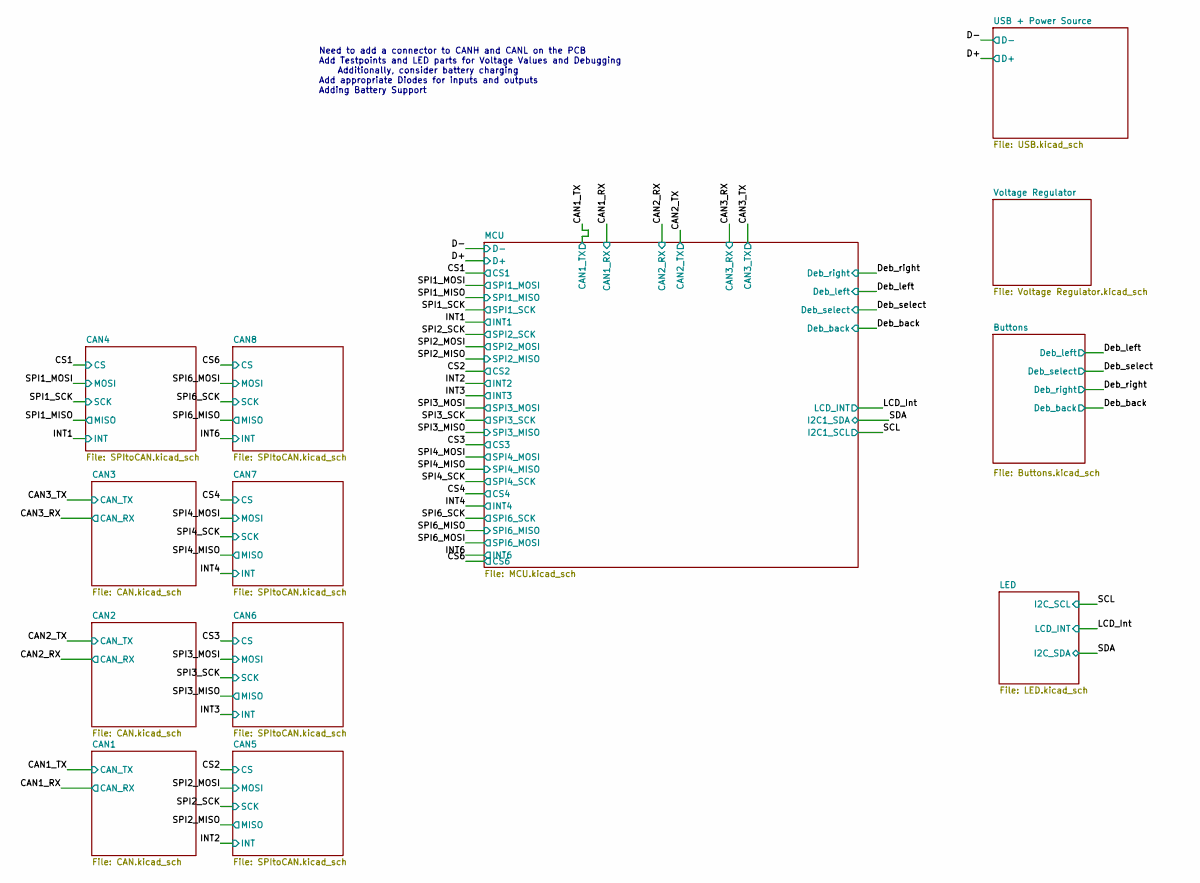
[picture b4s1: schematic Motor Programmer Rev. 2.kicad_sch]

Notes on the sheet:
Need to add a connector to CANH and CANL on the PCB Add Testpoints and LED parts for Voltage Values and Debugging Additionally, consider battery charging Add appropriate Diodes for inputs and outputs Adding Battery Support
